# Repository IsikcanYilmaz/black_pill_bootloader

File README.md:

~ L I G H T  C U B E ~

A "Cube of light" using panels full of WS2812B addressable LEDs, based on an STM32L453.

Current state of the project is:
 - LED panels glued and soldered into forming the 5 sides of the cube.
 - The panels work; STM devboard able to play animations and whatnot.
 - HW design should be done. Gotta order it
 
Need to do:
 - Order it, assemble it.
 - Get the nordic part to work, enable bluetooth. 

Prototype demo:
https://imgur.com/a/DEMgBDq

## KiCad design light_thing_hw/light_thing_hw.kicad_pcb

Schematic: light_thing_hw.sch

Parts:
C1, C2, C3, C4, C16, C17, C22, C23: 0.1uF; C_0603_1608Metric_Pad1.05x0.95mm_HandSolder; JLC_LIBRARY C14663
C5, C6: 1uF; C_0603_1608Metric_Pad1.05x0.95mm_HandSolder
C7, C19, C20: 220uF; C_0603_1608Metric_Pad1.05x0.95mm_HandSolder
C8, C10, C14, C18: 10uF; C_0603_1608Metric_Pad1.05x0.95mm_HandSolder
C9, C13: 100nF; C_0603_1608Metric_Pad1.05x0.95mm_HandSolder; JLC_LIBRARY C14663
C12: 1nF; C_0603_1608Metric_Pad1.05x0.95mm_HandSolder
C15: 2700pF; C_0603_1608Metric_Pad1.05x0.95mm_HandSolder
C21: 10nF; C_0603_1608Metric_Pad1.05x0.95mm_HandSolder; JLC_LIBRARY C14663
C24: 2.2uF; C_0603_1608Metric_Pad1.05x0.95mm_HandSolder; JLC_LIBRARY C14663
D1: 2.5A, 20V STPS2L60A; D_SMA
D2: GREEN LED; LED_0603_1608Metric_Pad1.05x0.95mm_HandSolder
D3: RED LED; LED_0603_1608Metric_Pad1.05x0.95mm_HandSolder
J1: CONNECTORS; PinHeader_2x05_P2.54mm_Vertical
J2: Li-Ion Battery; JST_SH_BM02B-SRSS-TB_1x02-1MP_P1.00mm_Vertical
J3: ADDR_LED_PANEL_1_CONNECTORS; PinHeader_2x02_P1.00mm_Vertical
J4: ADDR_LED_PANEL_2_CONNECTORS; PinHeader_2x02_P1.00mm_Vertical
J5: MIC_CONN; PinHeader_1x03_P1.00mm_Vertical
J6: 3V3_TP; PinHeader_2x01_P2.54mm_Vertical
L1: 10uH, 2.5A, B1047AS-100M=P3; IND_B1047AS-100M=P3
Q1: MMBF170; SOT-23
Q2: BSS83P; SOT-23
R1: 675; R_0603_1608Metric_Pad1.05x0.95mm_HandSolder; JLC_LIBRARY C21190
R2, R14: 1k; R_0603_1608Metric_Pad1.05x0.95mm_HandSolder; JLC_LIBRARY C21190
R3: 30.1k; R_0603_1608Metric_Pad1.05x0.95mm_HandSolder; JLC_LIBRARY C51221
R4, R17: 10k; R_0603_1608Metric_Pad1.05x0.95mm_HandSolder; JLC_LIBRARY C25804
R5: 10K; R_0603_1608Metric_Pad1.05x0.95mm_HandSolder; JLC_LIBRARY C25804
R6, R10, R11, R12, R13: 4.7k; R_0603_1608Metric_Pad1.05x0.95mm_HandSolder; JLC_LIBRARY C23162
R7: 100; R_0603_1608Metric_Pad1.05x0.95mm_HandSolder; JLC_LIBRARY C22775
R8, R9: 510; R_0603_1608Metric_Pad1.05x0.95mm_HandSolder; JLC_LIBRARY C23193
R15: 2k; R_0603_1608Metric_Pad1.05x0.95mm_HandSolder; JLC_LIBRARY C22975
R16: 357; R_0603_1608Metric_Pad1.05x0.95mm_HandSolder; JLC_LIBRARY C23028
R18: 300; R_0603_1608Metric_Pad1.05x0.95mm_HandSolder; JLC_LIBRARY C17617
SW1: EVQ-P7J01P; SW_EVQ-P7J01P
SW2: ST_RESET_BUTTON; SW_1437566-4
U1: BC832-V1; BC832-BC832_3d1
U2: BQ21040DBVT; SOT95P280X145-6N; JLC_LIBRARY C78978
U4: LMR62421XMF; SOT-23-5
U5: LP38511MRX-ADJ_NOPB
U6: STM32L476RGTx; LQFP-64_10x10mm_P0.5mm; JLC_LIBRARY C74797
U7: ICM-20600; PQFN50P250X300X97-14N; JLC_LIBRARY C124140
USB_MICRO_CONN1: USB_OTG; USB_Micro-B_Molex_47346-0001

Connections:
+3V3: C1.1, C2.1, C3.1, C4.1, C15.2, C16.1, C17.1, C18.2, C21.1, C22.1, C24.1, J6.1, Q2.2 (S), R6.1, R10.1, R11.1, R12.1, R13.1, R15.2, U1.P$16 (VDD), U5.1 (OUT), U5.2 (OUT), U6.1 (VBAT), U6.13 (VDDA), U6.19 (VDD), U6.32 (VDD), U6.48 (VDDUSB), U6.64 (VDD), U7.5 (VDDIO), U7.8 (VDD)
+5V: C7.1, C10.1, C12.1, C19.1, C20.1, D1.1 (K), J3.3, R3.1
+BATT: C6.1, C8.2, C14.1, J2.2, L1.1, R2.2, U2.2 (OUT), U4.5 (VIN), U5.6 (EN), U5.7 (IN), U5.8 (IN)
ACCEL_EXTI_1: U6.40 (PC9), U7.4 (INT1)
ACCEL_EXTI_2: U6.39 (PC8), U7.9 (INT2)
ADDR_LED_BACKUP_PWM: J4.2, U6.14 (PA0)
ADDR_LED_PANEL_1_PWM: R18.2, U6.27 (PB1)
BATT_ADC: R2.1, R14.1, U6.22 (PA6)
BATT_ADC_ENABLE: Q1.1 (G), U6.37 (PC6)
BOOST_ENABLE: U4.4 (EN), U6.38 (PC7)
BT_GPIO_0: U1.P$13 (P02/AIN0), U6.10 (PC2)
BT_GPIO_1: U1.P$12 (P01/XL2), U6.11 (PC3)
BT_GPIO_2: U1.P$11 (P00/XL1), U6.24 (PC4)
BT_GPIO_3: U1.P$9 (P03/AIN1), U6.25 (PC5)
BT_RED_LED: R9.2, U1.P$6 (P13)
BT_RST: J1.10, U1.P$10 (P21/RESET), U6.50 (PA15)
BT_RX: J1.2, U1.P$8 (P12/RX), U6.51 (PC10)
BT_SWCLK: J1.8, U1.P$4 (SWCLK)
BT_SWDIO: J1.9, U1.P$3 (SWDIO)
BT_TX: J1.4, U1.P$7 (P11/TX), U6.52 (PC11)
BUTTON1: C13.1, SW1.2_1, SW1.2_2, U6.2 (PC13)
CHARGER_STAT1: U2.3 (~CHG), U6.35 (PB14)
D+: U6.45 (PA12), USB_MICRO_CONN1.3
D-: U6.44 (PA11), USB_MICRO_CONN1.2
GND: C1.2, C2.2, C3.2, C4.2, C5.1, C6.2, C7.2, C8.1, C9.2, C10.2, C14.2, C16.2, C17.2, C18.1, C19.2, C20.2, C21.2, C22.2, C23.2, C24.2, D2.1 (K), D3.1 (K), J2.1, J3.1, J3.4, J5.3, J6.2, Q1.2 (S), R1.2, R4.2, R5.2, R6.2, R7.1, R16.1, R17.2, SW1.1_1, SW1.1_2, SW2.1, U1.P$1 (GND), U2.5 (GND), U4.2 (GND), U5.5 (GND), U5.9 (HEAT_TAB), U6.12 (VSSA), U6.18 (VSS), U6.31 (VSS), U6.47 (VSS), U6.63 (VSS), U7.1 (AD0/SDO), U7.6 (GND), U7.7 (RESV), U7.10 (FSYNC/NC), U7.12 (~CS), USB_MICRO_CONN1.5, USB_MICRO_CONN1.6
GREEN_LED: R8.2, U6.21 (PA5)
I2C1_SCL: J4.4, R11.2, U6.61 (PB8), U7.13 (SCL/SCLK)
I2C1_SDA: J4.3, R10.2, U6.62 (PB9), U7.14 (SDA/SDI)
I2C2_SCL: R13.2, U1.P$14 (P27/SCL), U6.34 (PB13)
I2C2_SDA: R12.2, U1.P$15 (P26/SDA), U6.30 (PB11)
MIC_3V3: J5.2, Q2.3 (D)
MIC_ENABLE: Q2.1 (G), U6.28 (PB2)
MIC_IN: J5.1, U6.26 (PB0)
unnamed: C12.2, R3.2, R4.1, U4.3 (FB)
unnamed: C13.2, R7.2
unnamed: C15.1, R15.1, R16.2, U5.3 (ADJ)
unnamed: C23.1, U7.11 (REGOUT)
unnamed: D1.2 (A), L1.2, U4.1 (SW)
unnamed: D2.2 (A), R8.1
unnamed: D3.2 (A), R9.1
unnamed: J3.2, R18.1
unnamed: Q1.3 (D), R14.2
unnamed: R1.1, U2.4 (ISET)
unnamed: R5.1, U6.60 (BOOT0)
unnamed: R17.1, U2.1 (TS)
RESET: C9.1, J1.6, SW2.2, U6.7 (NRST)
SWCLK: J1.5, U6.49 (PA14)
SWDIO: J1.7, U6.46 (PA13)
SWO: U6.55 (PB3)
TEST_GPIO0: U6.56 (PB4)
TEST_GPIO1: J4.1, U6.57 (PB5)
TEST_GPIO2: U6.53 (PC12)
USART_2_RX: J1.3, U6.17 (PA3)
USART_2_TX: J1.1, U6.16 (PA2)
VBUS: C5.2, U2.6 (VIN), USB_MICRO_CONN1.1

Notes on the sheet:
LIGHT CUBE MLB
MCU
POWER
BLE AND ACCEL
BATTERY: - 1100mAH, 40.5mm x 41.5mm x 6.1mm, li-po battery. (3.0V - 4.2V) https://www.digikey.com/product-detail/en/tinycircuits/ASR00008/1832-1044-ND/8680974
UART4 TX
UART4 RX

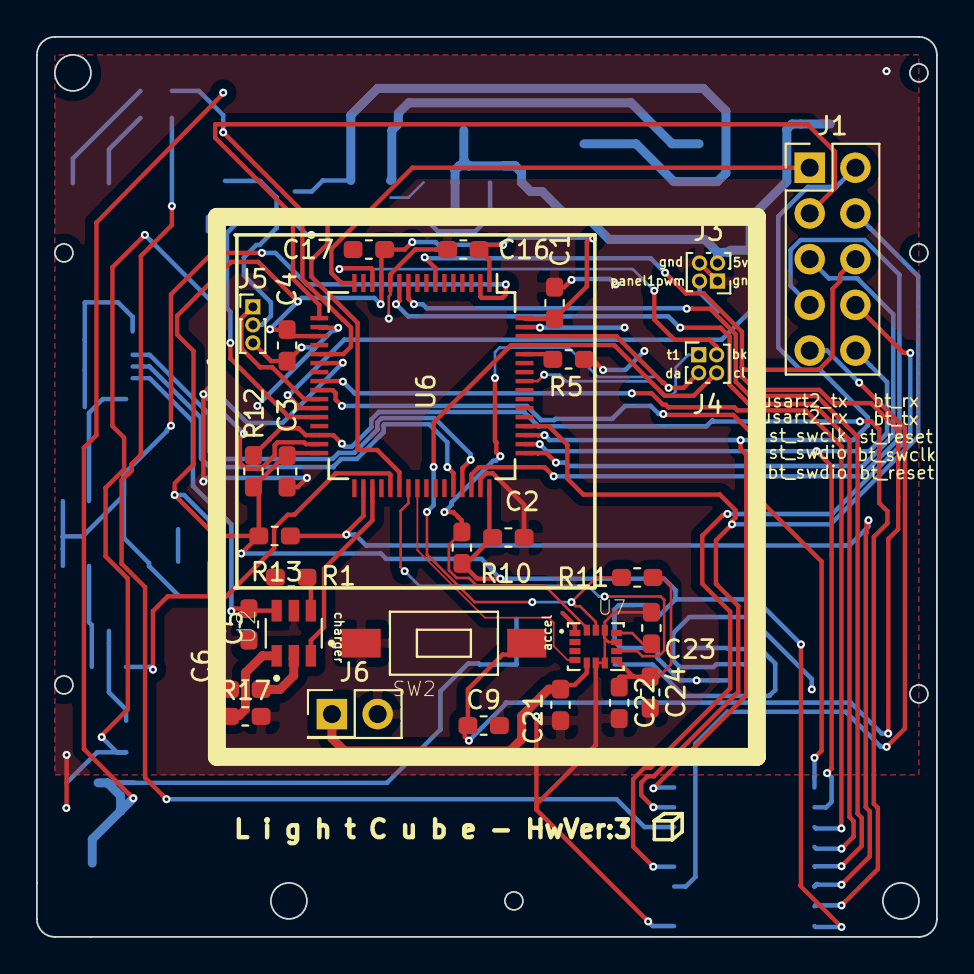
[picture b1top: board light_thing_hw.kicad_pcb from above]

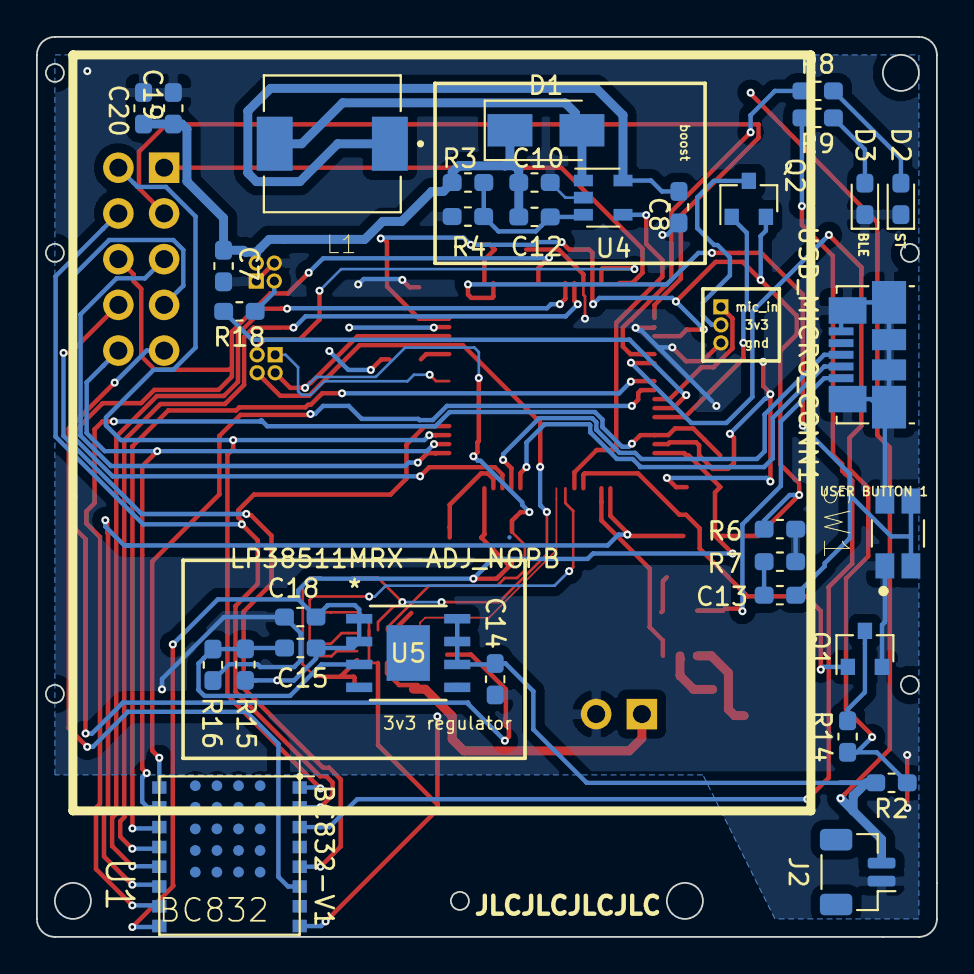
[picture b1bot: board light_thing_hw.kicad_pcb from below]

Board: 2 copper layers, 50.0 x 50.0 mm, 62 parts (33 on the bottom side), 52 nets.

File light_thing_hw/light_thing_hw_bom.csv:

Id,Designator,Package,Quantity,Designation,Reference / name,Supplier,Notes,unit price,multiplier,total
1,"C6,C5",C_0603_1608Metric_Pad1.05x0.95mm_HandSolder,2,1uF,CL10A105KP8NNNC,,,0.038,2,0.076
2,"C7,C19,C20",C_0603_1608Metric_Pad1.05x0.95mm_HandSolder,3,220uF,GRM31CC80G227ME11L,,,1.29,3,3.87
3,J5,PinHeader_1x03_P1.00mm_Vertical,1,MIC_CONN, ---,,,0,1,0
4,U5A1,LQFP-64-1EP_10x10mm_P0.5mm_EP6.5x6.5mm,1,STM32L452RETx,?STM32L452RET6?,,,7.1,1,7.1
5,"C1,C2,C3,C4,C16,C17",C_0603_1608Metric_Pad1.05x0.95mm_HandSolder,6,0.1uF,?C0603C104Z3VACTU?,,,0.031,6,0.186
6,"C8,C10,C14,C18",C_0603_1608Metric_Pad1.05x0.95mm_HandSolder,4,10uF,?GRM188R61A106KE69J?,,,0.148,4,0.592
7,"C9,C11,C13",C_0603_1608Metric_Pad1.05x0.95mm_HandSolder,3,100nF,C0603C104Z3VACTU,,,0.031,3,0.093
8,C12,C_0603_1608Metric_Pad1.05x0.95mm_HandSolder,1,1nF,?CC0603KRX7R9BB102?,,,0.1,1,0.1
9,C15,C_0603_1608Metric_Pad1.05x0.95mm_HandSolder,1,2700pF,?CC0603KRX7R9BB272?,,,0.1,1,0.1
10,D1,D_SOD-323_HandSoldering,1,"2.5A, 20V","PMEG4030EP,115? ",,,0.43,1,0.43
11,D2,LED_0603_1608Metric_Pad1.05x0.95mm_HandSolder,1,GREEN LED, ?LTST-C191KRKT? ,,,0.26,1,0.26
12,D3,LED_0603_1608Metric_Pad1.05x0.95mm_HandSolder,1,RED LED, ?LTST-C191KRKT? ,,,0.26,1,0.26
13,J1,PinHeader_2x05_P1.00mm_Vertical,1,CONNECTORS, ---,,,0,1,0
14,J2,Molex_PicoBlade_53261-0271_1x02-1MP_P1.25mm_Horizontal,1,Li-Ion Battery,?0532610271? WM7620CT-ND?,,,0.51,1,0.51
15,J3,PinHeader_2x02_P1.00mm_Vertical,1,ADDR_LED_PANEL_1_CONNECTORS, ---,,,0,1,0
16,J4,PinHeader_2x02_P1.00mm_Vertical,1,ADDR_LED_PANEL_2_CONNECTORS, ---,,,0,1,0
17,L1,L_0603_1608Metric_Pad1.05x0.95mm_HandSolder,1,"10uH, 2.5A",?CBMF1608T100K?,,this needs to change :(,2.59333,1,2.59333
18,Q1,SOT-23,1,MMBF170,?MMBF170LT1G?,,,0.28,1,0.28
19,"R1,R2,R14,R17",R_0603_1608Metric_Pad1.05x0.95mm_HandSolder,4,1k, ?RC0603JR-071KL? ,,,0.018,4,0.072
20,R3,R_0603_1608Metric_Pad1.05x0.95mm_HandSolder,1,30.1k,?RT0603BRD0730K1L?,,,0.35,1,0.35
21,R4,R_0603_1608Metric_Pad1.05x0.95mm_HandSolder,1,10k, ?RC0603FR-0710KL? ,,,0.022,1,0.022
22,R5,R_0603_1608Metric_Pad1.05x0.95mm_HandSolder,1,10K, ?RC0603FR-0710KL? ,,,0.022,1,0.022
23,"R6,R10,R11,R12,R13",R_0603_1608Metric_Pad1.05x0.95mm_HandSolder,5,4.7k, ?RC0603JR-074K7L? ,,,0.018,5,0.09
24,R7,R_0603_1608Metric_Pad1.05x0.95mm_HandSolder,1,100, ?RC0603FR-07100RL? ,,,0.022,1,0.022
25,"R8,R9",R_0603_1608Metric_Pad1.05x0.95mm_HandSolder,2,510, ?RC0603FR-07510RL? ,,,0.022,2,0.044
26,R15,R_0603_1608Metric_Pad1.05x0.95mm_HandSolder,1,2k, ?RC0603FR-072KL? ,,,0.022,1,0.022
27,R16,R_0603_1608Metric_Pad1.05x0.95mm_HandSolder,1,357, ?RC0603FR-07357RL? ,,,0.022,1,0.022
28,SW1,SW_SPST_B3U-3000P,1,ST_USER_BUTTON1,EVP-AKE31A? ,,,0.61,1,0.61
29,U1,BC832-BC832_3d1,1,BC832-V1, 1914-1017-1-ND ,,,11.66,1,11.66
30,U3,MCP73833T-FCIUN-SMD,1,MCP73833T-FCI_UN,MCP73833T-FCI/UN? ,,,0.85,1,0.85
31,U4,SOT-23-5,1,LMR62421XMF,LMR62421XMF/NOPB ,,,1.95,1,1.95
32,U5,LP38511MRX-ADJ_NOPB,1,LP38511MRX-ADJ_NOPB,LP38511MRX-ADJ/NOPB? ,,,1.77,1,1.77
33,USB_MICRO_CONN1,USB_Micro-B_Molex_47346-0001,1,USB_OTG,?0473461001? / WM11228CT-ND?,,,0.91,1,0.91
34,"TP1,TP2",TestPoint_Pad_D1.0mm,2,TestPoint, ---,,,0,2,0
35,U2,LGA-14_3x2.5mm_P0.5mm_LayoutBorder3x4y_modded,1,LSM6DS3,LSM6DS3TR? ,,,3.06,1,3.06
36,R18,R_0603_1608Metric_Pad1.05x0.95mm_HandSolder,1,300, ?RC0603FR-07300RL? ,,,0.022,1,0.022
37,Q2,SOT-23,1,BSS83P,BSS83PH6327XTSA1,,,0.41,1,0.41
38,SW2,SW_SPST_EVPBF,1,ST_RESET_BUTTON,,,,0,1,0
,,,,,,,,,,38.35833

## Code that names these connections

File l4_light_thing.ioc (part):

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Mcu.Name=STM32L452R(C-E)Tx
Mcu.Package=LQFP64
Mcu.UserName=STM32L452RETx
PA0.Signal=S_TIM2_CH1
PA1.Signal=S_TIM2_CH2
PA10.GPIOParameters=GPIO_Pu
PA10.GPIO_Pu=GPIO_PULLUP
PA10.Mode=I2C
PA10.Signal=I2C1_SDA
PA11.Mode=Device
PA11.Signal=USB_DM
PA12.Mode=Device
PA12.Signal=USB_DP
PA13\ (JTMS/SWDIO).GPIOParameters=GPIO_Label
PA13\ (JTMS/SWDIO).GPIO_Label=TMS
PA13\ (JTMS/SWDIO).Mode=Serial_Wire
PA13\ (JTMS/SWDIO).Signal=SYS_JTMS-SWDIO
PA14\ (JTCK/SWCLK).GPIOParameters=GPIO_Label
PA14\ (JTCK/SWCLK).GPIO_Label=TCK
PA14\ (JTCK/SWCLK).Mode=Serial_Wire
PA14\ (JTCK/SWCLK).Signal=SYS_JTCK-SWCLK
PA2.GPIOParameters=GPIO_Speed,GPIO_PuPd,GPIO_Label,GPIO_Mode
PA2.GPIO_Label=USART_TX
PA2.GPIO_Mode=GPIO_MODE_AF_PP
PA2.GPIO_PuPd=GPIO_PULLUP
PA2.GPIO_Speed=GPIO_SPEED_FREQ_VERY_HIGH
PA2.Mode=Asynchronous
PA2.Signal=USART2_TX
PA3.GPIOParameters=GPIO_Speed,GPIO_PuPd,GPIO_Label,GPIO_Mode
PA3.GPIO_Label=USART_RX
PA3.GPIO_Mode=GPIO_MODE_AF_PP
PA3.GPIO_PuPd=GPIO_PULLUP
PA3.GPIO_Speed=GPIO_SPEED_FREQ_VERY_HIGH
PA3.Mode=Asynchronous
PA3.Signal=USART2_RX
PA5.GPIOParameters=GPIO_Speed,GPIO_PuPd,GPIO_Label,GPIO_ModeDefaultOutputPP
PA5.GPIO_Label=LD4 [green Led]
PA5.GPIO_ModeDefaultOutputPP=GPIO_MODE_OUTPUT_PP
PA5.GPIO_PuPd=GPIO_NOPULL
PA5.GPIO_Speed=GPIO_SPEED_FREQ_LOW
PA5.Signal=GPIO_Output
PA6.GPIOParameters=GPIO_Label
PA6.GPIO_Label=BATT_ADC_IN
PA6.Signal=ADCx_IN11
PA9.GPIOParameters=GPIO_Pu
PA9.GPIO_Pu=GPIO_PULLUP
PA9.Mode=I2C
PA9.Signal=I2C1_SCL
PB0.Signal=ADCx_IN15
PB1.GPIOParameters=GPIO_Speed
PB1.GPIO_Speed=GPIO_SPEED_FREQ_VERY_HIGH
PB1.Signal=S_TIM3_CH4
PB10.Signal=S_TIM2_CH3
PB11.GPIOParameters=GPIO_Pu
PB11.GPIO_Pu=GPIO_PULLUP
PB11.Mode=I2C
PB11.Signal=I2C2_SDA
PB13.GPIOParameters=GPIO_Pu
PB13.GPIO_Pu=GPIO_PULLUP
PB13.Mode=I2C
PB13.Signal=I2C2_SCL
PB3\ (JTDO/TRACESWO).GPIOParameters=GPIO_Label
PB3\ (JTDO/TRACESWO).GPIO_Label=SWO
PB3\ (JTDO/TRACESWO).Signal=SYS_JTDO-SWO
PB6.GPIOParameters=GPIO_Label
PB6.GPIO_Label=ACCEL_EXTI_0
PB6.Signal=GPIO_Input
PB7.GPIOParameters=GPIO_Label
PB7.GPIO_Label=ACCEL_EXTI_1
PB7.Signal=GPIO_Input
PC10.GPIOParameters=GPIO_PuPd
PC10.GPIO_PuPd=GPIO_PULLUP
PC10.Mode=Asynchronous
PC10.Signal=UART4_TX
PC11.GPIOParameters=GPIO_PuPd
PC11.GPIO_PuPd=GPIO_PULLUP
PC11.Mode=Asynchronous
PC11.Signal=UART4_RX
PC13.GPIOParameters=GPIO_PuPd,GPIO_Label,GPIO_ModeDefaultEXTI
PC13.GPIO_Label=B1 [Blue PushButton]
PC13.GPIO_ModeDefaultEXTI=GPIO_MODE_IT_RISING_FALLING
PC13.GPIO_PuPd=GPIO_PULLDOWN
PC13.Signal=GPXTI13
PC14-OSC32_IN\ (PC14).Mode=LSE-External-Oscillator
PC14-OSC32_IN\ (PC14).Signal=RCC_OSC32_IN
PC15-OSC32_OUT\ (PC15).Mode=LSE-External-Oscillator
PC15-OSC32_OUT\ (PC15).Signal=RCC_OSC32_OUT
PC2.GPIOParameters=GPIO_Label
PC2.GPIO_Label=BT_GPIO_0
PC2.Signal=GPIO_Output
PC3.GPIOParameters=GPIO_Label
PC3.GPIO_Label=BT_GPIO_1
PC3.Signal=GPIO_Output
PC4.GPIOParameters=GPIO_Label
PC4.GPIO_Label=BT_GPIO_2
PC4.Signal=GPIO_Output
PC5.GPIOParameters=GPIO_Label
PC5.GPIO_Label=BT_GPIO_3
PC5.Signal=GPIO_Output
PC6.GPIOParameters=GPIO_Label
PC6.GPIO_Label=BATT_ADC_ENABLE
PC6.Signal=GPIO_Output
PC7.Signal=S_TIM3_CH2
PH0-OSC_IN\ (PH0).Signal=RCC_OSC_IN
PH1-OSC_OUT\ (PH1).Signal=RCC_OSC_OUT
RCC.HSE_VALUE=8000000
RCC.SYSCLKFreq_VALUE=80000000
RCC.SYSCLKSource=RCC_SYSCLKSOURCE_PLLCLK
board=NUCLEO-L452RE
boardIOC=true

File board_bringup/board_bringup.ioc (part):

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PC7.GPIOParameters=PinState,GPIO_Label
Mcu.UserName=STM32L476RGTx
PB14.GPIO_Label=CHARGER_STAT1
PC6.GPIO_Label=BATT_ADC_EN
PA11.Mode=Device_Only
PA6.GPIO_Label=BATT_ADC
PB0.GPIO_Label=MIC_IN_ADC
PB11.Signal=I2C2_SDA
PB13.Signal=I2C2_SCL
PB15.Signal=GPIO_Input
RCC.SYSCLKSource=RCC_SYSCLKSOURCE_PLLCLK
PA14\ (JTCK-SWCLK).Signal=SYS_JTCK-SWCLK
PA12.Signal=USB_OTG_FS_DP
PC7.Signal=GPIO_Output
RCC.HSE_VALUE=8000000
PB2.Signal=GPIO_Output
PB0.GPIOParameters=GPIO_Label
PA5.GPIO_PuPd=GPIO_PULLUP
PC7.PinState=GPIO_PIN_SET
Mcu.Package=LQFP64
PB9.Signal=I2C1_SDA
PB1.Signal=S_TIM3_CH4
PA6.Signal=ADCx_IN11
PA5.GPIOParameters=GPIO_PuPd,GPIO_Label
PB14.GPIOParameters=GPIO_Label
PB13.Mode=I2C
PA13\ (JTMS-SWDIO).Signal=SYS_JTMS-SWDIO
PA6.GPIOParameters=GPIO_Label
PA14\ (JTCK-SWCLK).Mode=Serial_Wire
PC6.Signal=GPIO_Output
PB11.Mode=I2C
PB9.Mode=I2C
PB2.GPIOParameters=GPIO_Label
PB14.Signal=GPIO_Input
PA5.Signal=GPIO_Output
board=custom
PB15.GPIO_Label=CHARGER_STAT2
PB15.GPIOParameters=GPIO_Label
Mcu.Name=STM32L476R(C-E-G)Tx
PC7.GPIO_Label=BOOST_EN
PA13\ (JTMS-SWDIO).Mode=Serial_Wire
RCC.SYSCLKFreq_VALUE=80000000
PA12.Mode=Device_Only
PA5.GPIO_Label=GREEN_LED
PA11.Signal=USB_OTG_FS_DM
PB2.GPIO_Label=MIC_EN
PC6.GPIOParameters=GPIO_Label
PB8.Mode=I2C
PB8.Signal=I2C1_SCL
PB0.Signal=ADCx_IN15

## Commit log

2020-03-29 first
2020-03-29 correct mcu picked
2020-03-29 started working on timer1. 1 second frequency blinks
2020-03-30 pwm first pass
2020-04-01 enabled rgb channels
2020-04-02 led.c created
2020-04-13 USB stuff begun
2020-04-13 usb cdc ascii reception works
2020-04-20 usb com port echoes back
2020-04-20 minor updates. dfu begun
2020-04-22 bootloader begun
2020-04-22 cleanup
2020-04-25 need to test out the AddrLED comms
2020-05-02 updates. need to handle this in the timer/pwm
2020-05-03 PWM produces desired wave for the ws2818b
2020-05-03 PWM produces desired wave for the ws2818b. UPDATED
2020-05-03 struggling with dma
2020-05-04 the DMA issue not solved, but these ARR/CCR values _may_ be still good enough/among tolerance
2020-05-04 comments
2020-05-04 some progress. need to work on the LED IC's protocol
2020-05-05 arduino test added
2020-05-06 updates. right before my blackpill bricked
2020-05-08 blackpill bricked. moving onto L4-disco board
2020-05-09 L4 able to light all LEDs just like the arduino. the problem was the LED strip not getting enough voltage
2020-05-10 able to convert Pixel_ts into PixelPacket_ts
2020-05-10 animation test done. looks real neat
2020-05-22 2 panels work
2020-05-22 current draw survey code
2020-05-24 led flash problem solved
2020-05-29 checkpoint before trying out c u b e
2020-05-30 memory problem seems to be fixed wooo
2020-05-30 updates. beginning working on animations
2020-05-30 neat random fade animation done
2020-05-30 new modules/files
2020-05-30 done a survey on the random fade animation. and minor other things
2020-05-31 what used to be the addressing test (random triangles) is now an animation module. some cleanups
2020-06-01 updates. lookin neat
2020-06-03 minor changes
2020-06-03 project restructure
2020-06-03 readme updates
2020-06-04 added preview image
2020-06-04 pic on readme
2020-06-05 kicad files added
2020-06-07 updates on hw design. it seems like we can make it on a 3x3cm pcb. layout needs work
2020-06-08 wrote python program that emulates the light cube. refer to tools/pixel_testbench
2020-06-11 updates on random fade animation
2020-06-13 hw updates
2020-06-20 updates on pixel testbench
2020-06-20 pixel bench color test animation
2020-06-21 testbench updates
2020-06-21 made 5cm pcb. need to do routing etc.
2020-06-21 updates on hsv/hsl stuff. trying to get em to work
2020-06-22 hsv to rgb in c work
2020-06-22 rainbow hsv seems done. need to convert varibles from double to uints
2020-06-24 implemented rainbow
2020-06-25 rainbow breathing looks really nice
2020-06-27 hw updates. sw initd new needed peripherals. some changes on pixel testbench
2020-06-27 nucleo board needs work to enable uart. halting uart work until hardware arrives
2020-06-27 button handling begun
2020-06-28 software timers work
2020-06-28 button debounce done
2020-06-28 button debounce works. need to write button manager
2020-07-01 redone layout
2020-07-07 gonna make the vvias now
2020-07-07 about to do routing
2020-07-07 placing modules
2020-07-08 restarting routing
2020-07-08 doing well actually
2020-07-10 gonna add gnd now
2020-07-10 need to go thru drc
2020-07-11 hw not lookin bad ngl
2020-07-12 updates on sw. moving to a more eventful structured runtime
2020-07-12 makefile changes
2020-07-12 added MIC_IN to hardware and in stmcube
2020-07-13 some sw changes. about to add another mosfet switch to the board for the mic
2020-07-17 minor bugfix
2020-07-18 fixed animation skipping
2020-07-19 randomtriangles fade up bug fixed
2020-07-19 about to change user button
2020-07-19 hw updates. sent to print
2020-07-28 Set theme jekyll-theme-minimal
2020-08-12 about to redo hw for reordering
2020-08-19 moved to STM32L476
2020-09-11 about to change diode footprint to something thats available in digikey
2020-10-04 picked new reset button and diode footprint
2020-10-30 original accel footprint brought back
2020-11-01 Revert "original accel footprint brought back"
    This reverts commit 1c0a72e440ebf297838d42435a20a925d577f884.
2020-11-01 reverted the accelerometer footprint
2020-12-25 board bringup time
2020-12-25 board works programs, prints on cDc
2021-01-09 tested batt adc. works
2021-01-16 mistakes were made in hw rev2. off to rev 3. board_bringup directory works and plays animations.
2021-01-17 rev 3 work begun. changed battery connector, pulled down therm pin, broke out i2c1 pins. need to get a new accelerometer
2021-01-18 using new accelerometer icm-20600
2021-01-24 changed the inductor footprint to something that will work
2021-01-29 changed charger, reset button footprint
2021-02-01 changed userbutton and connector footprints
2022-08-12 eyyy still works on the nucleo devboard
2022-11-27 fixed button polarity setting and additions to dbg uart handling
2022-11-27 added backspace to dbg uart
2022-11-28 cmd str parsing
2023-01-17 added gitignore
2023-01-17 added lines animation

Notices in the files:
parts and their libraries:
Copyright 2016 Accelerated Designs. All rights reserved.
